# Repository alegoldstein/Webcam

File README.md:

# Webcam
Objective:
Create a webcam from scratch, including PCB, firmware, and enclosure

Steps Taken:
- Used KiCAD to design a compact 50 mm × 50 mm custom PCB integrating a microcontroller, ESP32 module, camera interface,  input buttons, status LEDs, power regulation circuitry, and passive components.
- Developed embedded firmware in Microchip Studio to enable controlled image capture and system-level communication.
- Implemented multiple communication protocols, including UART and SPI for MCU–ESP32 data exchange and debugging, and  I²C for camera initialization.
- Designed a 3D printed enclosure providing access to buttons and power, visibility for indicator LEDs, and support for wall mounting.

Outcome:
A functional webcam that streams images to the web when there is a connected client.

<p align="center">
  
  <br>
  <em>PCB Schematic</em>
</p>

<p align="center">
  
  <br>
  <em>Routing of PCB</em>
</p>

<table align="center">
  <tr>
    <td align="center">
      <br>
      <em>Assembled PCB (hand soldered)</em>
    </td>
    <td align="center">
      <br>
      <em>PCB inside of 3D printed box</em>
    </td>
    <td align="center">
      <br>
      <em>Final product</em>
    </td>
  </tr>
</table>

<p align="center">
  
  <br>
  <em>Live streaming of webcam to website</em>
</p>

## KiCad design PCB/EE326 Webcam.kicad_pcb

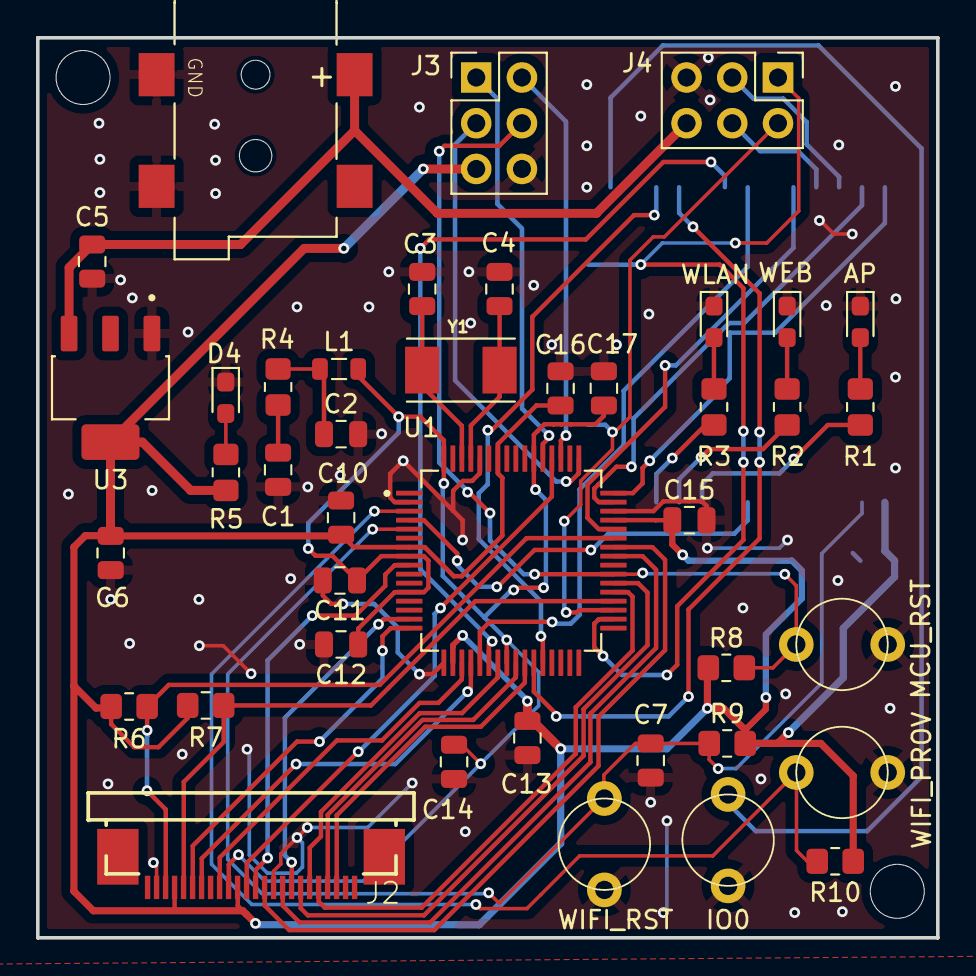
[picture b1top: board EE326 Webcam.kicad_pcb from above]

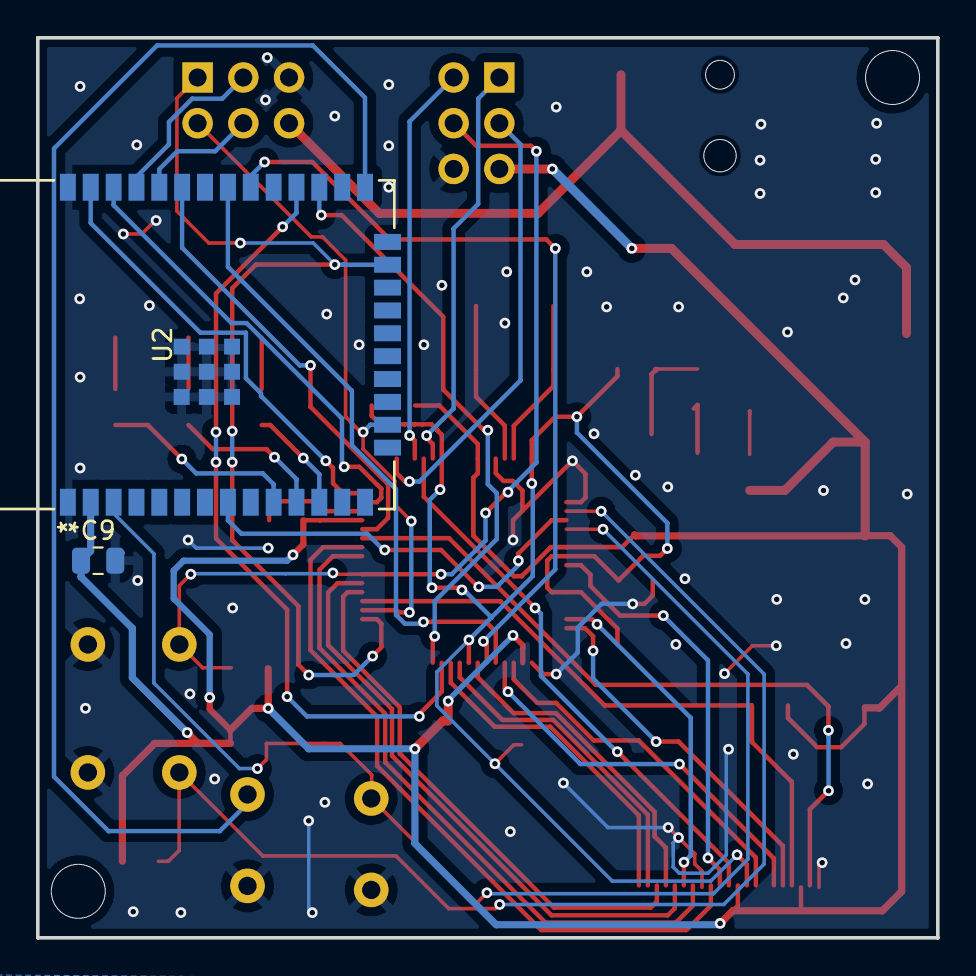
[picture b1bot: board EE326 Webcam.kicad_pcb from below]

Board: 2 copper layers, 50.0 x 50.0 mm, 43 parts (2 on the bottom side), 49 nets.

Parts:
AP: LED; LED_0603_1608Metric_Pad1.05x0.95mm_HandSolder
C1: 4.7uF; C_0805_2012Metric
C2, C9, C10, C11, C12, C13, C14, C15, C16, C17: 0.1uF; C_0805_2012Metric
C3, C4: 18pF; C_0805_2012Metric
C5, C6, C7: 1uF; C_0805_2012Metric
D4: LED; LED_0603_1608Metric_Pad1.05x0.95mm_HandSolder
IO0: SW_Push; pushbutton
J2: 2-1734592-4; CAM_CONN
J3, J4: Conn_02x03_Counter_Clockwise; PinHeader_2x03_P2.54mm_Vertical
L1: 10uH; L_0805_2012Metric
MCU_RST: SW_Push; pushbutton
R1, R2, R3, R5: 330R; R_0805_2012Metric_Pad1.20x1.40mm_HandSolder
R4: 1R0; R_0805_2012Metric_Pad1.20x1.40mm_HandSolder
R6, R7: 1k; R_0805_2012Metric_Pad1.20x1.40mm_HandSolder
R8, R9, R10: 10k; R_0805_2012Metric_Pad1.20x1.40mm_HandSolder
U1: ATSAM4S8BA-AU; atsam4s8b
U2: ESP32-WROOM-32E-N4; ESP32­WROOM­32E_EXP
U3: LDL1117S30R; voltage regulator
WEB: LED; LED_0603_1608Metric_Pad1.05x0.95mm_HandSolder
WIFI_PROV: SW_Push; pushbutton
WIFI_RST  : SW_Push; pushbutton
WLAN: LED; LED_0603_1608Metric_Pad1.05x0.95mm_HandSolder
Y1: ABM7-12.000MHZ-D2Y-T; crystal clock
barreljack1: DCJACK_2MM_SMT

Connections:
+1V2: C11.1, C12.1, C14.1, C17.1, J2.15, L1.1, U1.8 (VDDOUT), U1.12 (VDDCORE), U1.24 (VDDCORE__1), U1.54 (VDDCORE__2), U1.64 (VDDPLL)
+3V0: C6.1, C9.1, C10.1, C13.1, C15.1, C16.1, J2.14, J2.21, J3.5, R5.1, R6.1, R7.1, R8.2, R9.2, R10.2, U1.7 (VDDIN), U1.18 (VDDIO), U1.45 (VDDIO__1), U1.58 (VDDIO__2), U2.2 (3V3), U3.4 (VOUT__1)
+5V: C5.1, J4.6, U3.3 (VIN), barreljack1.PWR1 (PWR)
/CTRL1: U1.44 (PA2/PGMEN2), U2.33 (IO21)
/CTRL2: U1.47 (PA1/PGMEN1), U2.36 (IO22)
/CTRL3: U1.48 (PA0/PGMEN0), U2.37 (IO23)
/CTRL4: U1.4 (PB1/AD5), U2.8 (IO32)
/D0: J2.6, U1.23 (PA24/PGMD12)
/D1: J2.4, U1.25 (PA25/PGMD13)
/D2: J2.3, U1.26 (PA26/PGMD14)
/D3: J2.5, U1.37 (PA27/PGMD15)
/D4: J2.7, U1.38 (PA28)
/D5: J2.9, U1.41 (PA29)
/D6: J2.11, U1.42 (PA30)
/D7: J2.13, U1.52 (PA31)
/HREF: J2.16, U1.19 (PA16/PGMD4)
/IO0: IO0.1, U2.25 (IO0)
/LED1: R1.1, U2.10 (IO25)
/LED2: R2.1, U2.11 (IO26)
/LED3: R3.1, U2.12 (IO27)
/MISO: U1.27 (PA12/PGMD0), U2.28 (IO17)
/MOSI: U1.22 (PA13/PGMD1), U2.30 (IO18)
/NRST: J3.4, MCU_RST.1, R8.1, U1.39 (~NRST)
/PCLK: J2.8, U1.15 (PA23/PGMD11)
/RST_CAM: J2.19, U1.16 (PA20/PGMD8/AD3)
/RX_DEBUG: J4.3, U2.35 (TXD0)
/SCK: U1.21 (PA14/PGMD2), U2.31 (IO19)
/SCL: J2.20, R7.2, U1.36 (PA4/PGMNCMD)
/SDA: J2.22, R6.2, U1.43 (PA3)
/SWDCLK: J3.1, U1.53 (TCK/SWCLK/PB7)
/SWDIO: J3.2, U1.51 (TMS/SWDIO/PB6)
/SWO: J3.3, U1.49 (TDO/TRACESWO/PB5)
/TX_DEBUG: J4.4, U2.34 (RXD0)
/VSYNC: J2.18, U1.20 (PA15/PGMD3)
/WIFI_CS: U1.28 (PA11/PGMM3), U2.27 (IO16)
/WIFI_PROV: R10.1, U1.3 (PB0/AD4), WIFI_PROV.1
/WIFI_RST: C7.1, R9.1, U1.5 (PB2/AD6), U2.3 (EN), WIFI_RST.1
/WIFI_RX: J4.1, U1.34 (PA6/PGMNOE), U2.23 (IO15)
/WIFI_TX: J4.2, U1.35 (PA5/PGMRDY), U2.16 (IO13)
/XCLK: J2.12, U1.9 (PA17/PGMD5/AD0)
/XTAL1: C3.1, U1.62 (XIN/PGMCK/PB9), Y1.1
/XTAL2: C4.1, U1.61 (XOUT/PB8), Y1.2
GND: AP.1 (K), C1.2, C2.2, C3.2, C4.2, C5.2, C6.2, C7.2, C9.2, C10.2, C11.2, C12.2, C13.2, C14.2, C15.2, C16.2, C17.2, D4.1 (K), IO0.2, J2.10, J2.23, J3.6, J4.5, MCU_RST.2, U1.2 (GND), U1.17 (GND__1), U1.46 (GND__2), U1.60 (GND__3), U2.1 (GND), U2.38 (GND), U2.39 (GND), U2.40 (GND), U2.41 (GND), U2.42 (GND), U2.43 (GND), U2.44 (GND), U2.45 (GND), U2.46 (GND), U2.47 (GND), U3.1 (GND), WEB.1 (K), WIFI_PROV.2, WIFI_RST.2, WLAN.1 (K), barreljack1.GND, barreljack1.GNDBREAK
unnamed: C1.1, R4.2
unnamed: C2.1, L1.2, R4.1
unnamed: AP.2 (A), R1.2
unnamed: R2.2, WEB.2 (A)
unnamed: R3.2, WLAN.2 (A)
unnamed: D4.2 (A), R5.2

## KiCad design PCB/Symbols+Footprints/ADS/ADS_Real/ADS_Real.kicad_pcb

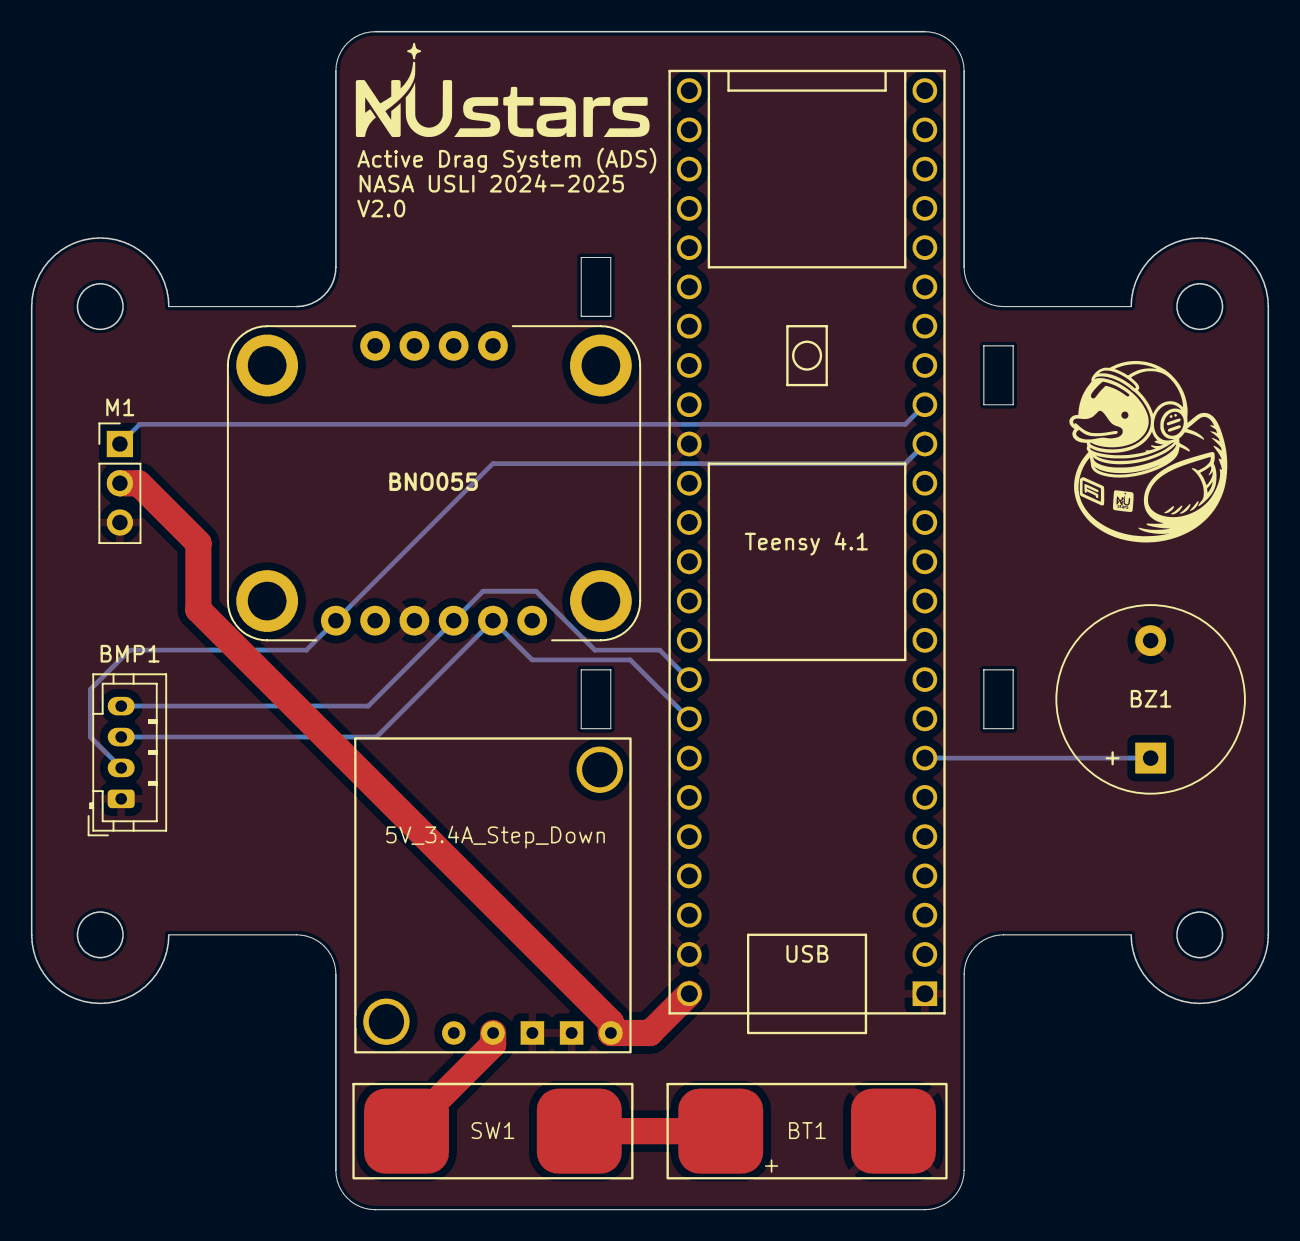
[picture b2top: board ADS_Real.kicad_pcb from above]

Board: 2 copper layers, 80.0 x 76.2 mm, 8 parts (0 on the bottom side), 9 nets.

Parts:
5V_3.4A_Step_Down1: 5V_3.4A_Step_Down
BMP1: JST_PH_B4B-PH-K_1x04_P2.00mm_Vertical
BT1: LiPo; SolderPad_5.5mm_2Pads_Directional
BZ1: Buzzer; Buzzer_12x9.5RM7.6
M1: Motor_Servo; PinHeader_1x03_P2.54mm_Vertical
SW1: Pull_Pin; SolderPad_5.5mm_2Pads_Bidirectional
Teensy 4.1: Teensy4.1; Teensy41
U2: BNO055

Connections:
+7.4V: BT1.1 (+), SW1.2 (B)
/Buzzer_In: BZ1.1 (+), Teensy 4.1.7 (5_IN2)
/Pull_Pin_Input: 5V_3.4A_Step_Down1.2 (VIN), SW1.3 (C)
/Pull_Pin_Output: 5V_3.4A_Step_Down1.5 (VOUT), M1.2 (+), Teensy 4.1.48 (VIN)
/SCL: BMP1.3 (SCL), Teensy 4.1.41 (19_A5_SCL), U2.5 (SCL)
/SDA: BMP1.4 (SDA), Teensy 4.1.40 (18_A4_SDA), U2.4 (SDA)
/Sensor_VIN: BMP1.2 (VIN), Teensy 4.1.15 (3V3), U2.1 (VIN)
/Servo_Signal: M1.1 (PWM), Teensy 4.1.16 (24_A10_TX6_SCL2)
GND: 5V_3.4A_Step_Down1.3 (GND), 5V_3.4A_Step_Down1.4 (GND), BMP1.1 (GND), BT1.2 (-), BZ1.2 (-), M1.3 (-), Teensy 4.1.1 (GND), Teensy 4.1.34 (GND), Teensy 4.1.47 (GND), U2.3 (GND)

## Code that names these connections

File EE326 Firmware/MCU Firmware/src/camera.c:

#include <asf.h>
#include "camera.h"
#include "conf_board.h"
#include "conf_clock.h"
#include <stdint.h>
#include <stdio.h>
#include "pio.h"
#include "ov2640.h"


/* Vsync signal information (true if it's triggered and false otherwise) */
static volatile uint32_t g_ul_vsync_flag = 0;

volatile uint32_t image_len;

uint8_t g_p_uc_cap_dest_buf[CAP_BUFFER_SIZE];

///////////////////////////////////////////////////////
//handler for rising edge of vsync, set flag
///////////////////////////////////////////////////////
void vsync_handler(uint32_t ul_id, uint32_t ul_mask){
    unused(ul_id);
	unused(ul_mask);

	g_ul_vsync_flag = true;
}


///////////////////////////////////////////////////////
//configure vsync interrupt
///////////////////////////////////////////////////////
void init_vsync_interrupts(){
    pio_handler_set(PIN_VSYNC_PIO,          // PIOA base pointer
                    OV2640_VSYNC_ID,        // ID_PIOA
                    OV2640_VSYNC_MASK,      // 1 << 15
                    OV2640_VSYNC_TYPE,      // PIO_IT_RISE_EDGE
                    vsync_handler);

    NVIC_EnableIRQ((IRQn_Type) OV2640_VSYNC_ID);
}


///////////////////////////////////////////////////////
//configure TWI (two wire interface I2C)
///////////////////////////////////////////////////////
void configure_twi(){
    twi_options_t opt;

	pmc_enable_periph_clk(ID_TWI0);

	gpio_configure_pin(PIO_PA3A_TWD0,  PIO_PERIPH_A | PIO_PULLUP);
	gpio_configure_pin(PIO_PA4A_TWCK0, PIO_PERIPH_A | PIO_PULLUP);

    // Setup TWI options
    opt.master_clk = sysclk_get_cpu_hz();
    opt.speed      = 100000;        // 100kHz standard mode
    opt.chip       = 0x30;          // OV2640 SCCB write address

    // Initialize TWI Master
    twi_master_init(TWI0, &opt);
}



///////////////////////////////////////////////////////
//configure and initialize parallel capture 
///////////////////////////////////////////////////////
void pio_capture_init(Pio *p_pio, uint32_t ul_id){
	
/* Enable periphral clock */
	pmc_enable_periph_clk(ul_id);

	/* Disable pio capture */
	p_pio->PIO_PCMR &= ~((uint32_t)PIO_PCMR_PCEN);

	/* Disable rxbuff interrupt */
	p_pio->PIO_PCIDR |= PIO_PCIDR_RXBUFF;

	/* 32bit width*/
	p_pio->PIO_PCMR &= ~((uint32_t)PIO_PCMR_DSIZE_Msk);
	p_pio->PIO_PCMR |= PIO_PCMR_DSIZE_WORD;

	/* Only HSYNC and VSYNC enabled */
	p_pio->PIO_PCMR &= ~((uint32_t)PIO_PCMR_ALWYS);
	p_pio->PIO_PCMR &= ~((uint32_t)PIO_PCMR_HALFS);

#if !defined(DEFAULT_MODE_COLORED)
	/* Samples only data with even index */
	p_pio->PIO_PCMR |= PIO_PCMR_HALFS;
	p_pio->PIO_PCMR &= ~((uint32_t)PIO_PCMR_FRSTS);
#endif
}



///////////////////////////////////////////////////////
//use parallel capture and PDC to store images in buffer
///////////////////////////////////////////////////////
uint8_t pio_capture_to_buffer(Pio *p_pio, uint8_t *uc_buf, uint32_t ul_size){
/* Check if the first PDC bank is free */
	if ((p_pio->PIO_RCR == 0) && (p_pio->PIO_RNCR == 0)) {
		p_pio->PIO_RPR = (uint32_t)uc_buf;
		p_pio->PIO_RCR = ul_size;
		p_pio->PIO_PTCR = PIO_PTCR_RXTEN;
		return 1;
	} else if (p_pio->PIO_RNCR == 0) {
		p_pio->PIO_RNPR = (uint32_t)uc_buf;
		p_pio->PIO_RNCR = ul_size;
		return 1;
	} else {
		return 0;
	}
}



///////////////////////////////////////////////////////
//finds image length based on JPED protocol, can find start of image (SOI) before end of image 
///////////////////////////////////////////////////////(EOI)
//return 1 if success 0 and 0 if failure
uint8_t find_image_len(){
    uint8_t *buf = g_p_uc_cap_dest_buf;
    uint32_t i;

    // Verify SOI marker at the start (0xFF 0xD8)
    if (buf[0] != 0xFF || buf[1] != 0xD8){
        image_len = 0;
        return 0;   // no valid JPEG start found
    }

    // Scan for EOI marker (0xFF 0xD9)
    for (i = 2; i < CAP_BUFFER_SIZE - 1; i++){
        if (buf[i] == 0xFF && buf[i + 1] == 0xD9){
            image_len = i + 2;  // include the EOI marker itself
            return 1;
        }
    }

    // EOI not found
    image_len = 0;
    return 0;
}


///////////////////////////////////////////////////////
//configure camera pins and clk (XCLK), and call configure_twi()
///////////////////////////////////////////////////////
//not sure if this is the right to copy and paste, capture_init in ov7440 ex
void init_camera(){
// Data bus (camera -> MCU)
gpio_configure_pin(PIN_D0, PIO_INPUT);
gpio_configure_pin(PIN_D1, PIO_INPUT);
gpio_configure_pin(PIN_D2, PIO_INPUT);
gpio_configure_pin(PIN_D3, PIO_INPUT);
gpio_configure_pin(PIN_D4, PIO_INPUT);
gpio_configure_pin(PIN_D5, PIO_INPUT);
gpio_configure_pin(PIN_D6, PIO_INPUT);
gpio_configure_pin(PIN_D7, PIO_INPUT);

// Timing signals (camera -> MCU)
gpio_configure_pin(PIN_CAM_PCLK, PIO_INPUT);
gpio_configure_pin(PIN_HREF, PIO_INPUT);
gpio_configure_pin(PIN_VSYNC, PIO_INPUT | PIO_PULLUP);

gpio_configure_pin(PIN_CAM_XCLK, PIO_PERIPH_B);
pmc_enable_pck(PMC_PCK_0);
pmc_switch_pck_to_mainck(PMC_PCK_0, PMC_PCK_PRES_CLK_1);

// Reset (MCU -> camera)
// OV2640 reset is active LOW, so default HIGH = not in reset
gpio_configure_pin(PIN_CAM_RST, PIO_OUTPUT_1);
pio_capture_init(OV2640_DATA_BUS_PIO, OV2640_DATA_BUS_ID);
configure_twi();
}


//////////////////////////////////////////////////
//configure 0v2640 registers
//////////////////////////////////////////////////
void configure_camera(){
	ov_configure(BOARD_TWI, JPEG_INIT);
	ov_configure(BOARD_TWI, YUV422);
	ov_configure(BOARD_TWI, JPEG);
	ov_configure(BOARD_TWI, JPEG_320x240);
}

//////////////////////////////////////////////////
//capture image on rising edge of vsync and gets image length
//////////////////////////////////////////////////
uint8_t start_capture(){
    g_ul_vsync_flag = 0;
    pio_enable_interrupt(PIN_VSYNC_PIO, OV2640_VSYNC_MASK);
    while (!g_ul_vsync_flag) {
	}
    pio_disable_interrupt(PIN_VSYNC_PIO, OV2640_VSYNC_MASK);
    g_ul_vsync_flag = 0;

    pio_capture_enable(OV2640_DATA_BUS_PIO);
    pio_capture_to_buffer(OV2640_DATA_BUS_PIO, g_p_uc_cap_dest_buf,
            CAP_BUFFER_SIZE >> 2);
    while (!((OV2640_DATA_BUS_PIO->PIO_PCISR & PIO_PCIMR_RXBUFF) == PIO_PCIMR_RXBUFF)) {}
    pio_capture_disable(OV2640_DATA_BUS_PIO);

    // find image length and return success/fail
    return find_image_len();
}
